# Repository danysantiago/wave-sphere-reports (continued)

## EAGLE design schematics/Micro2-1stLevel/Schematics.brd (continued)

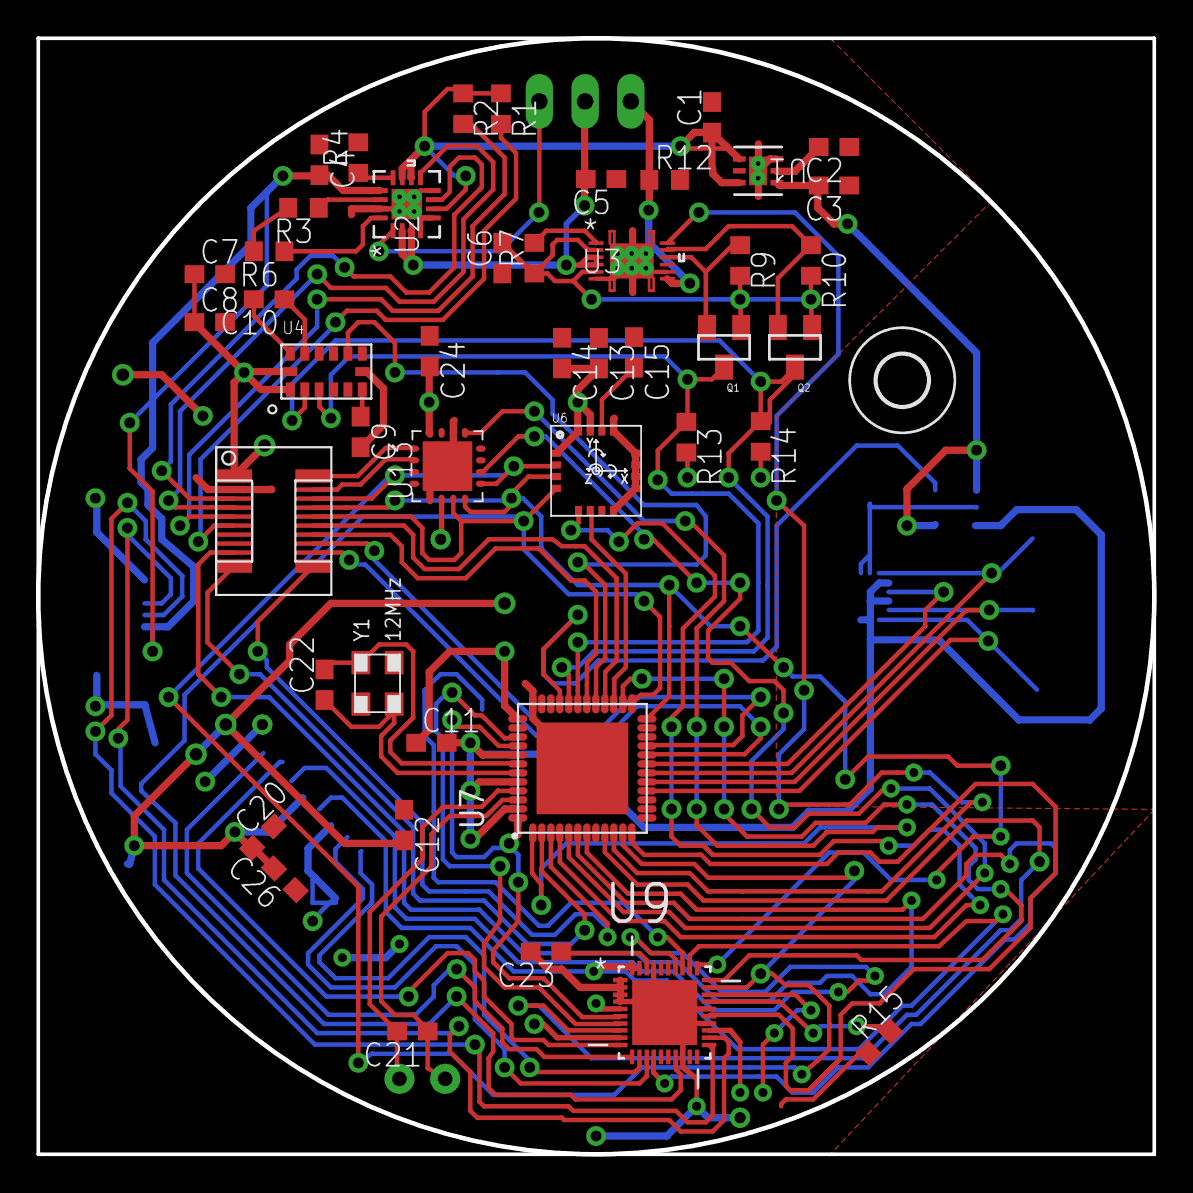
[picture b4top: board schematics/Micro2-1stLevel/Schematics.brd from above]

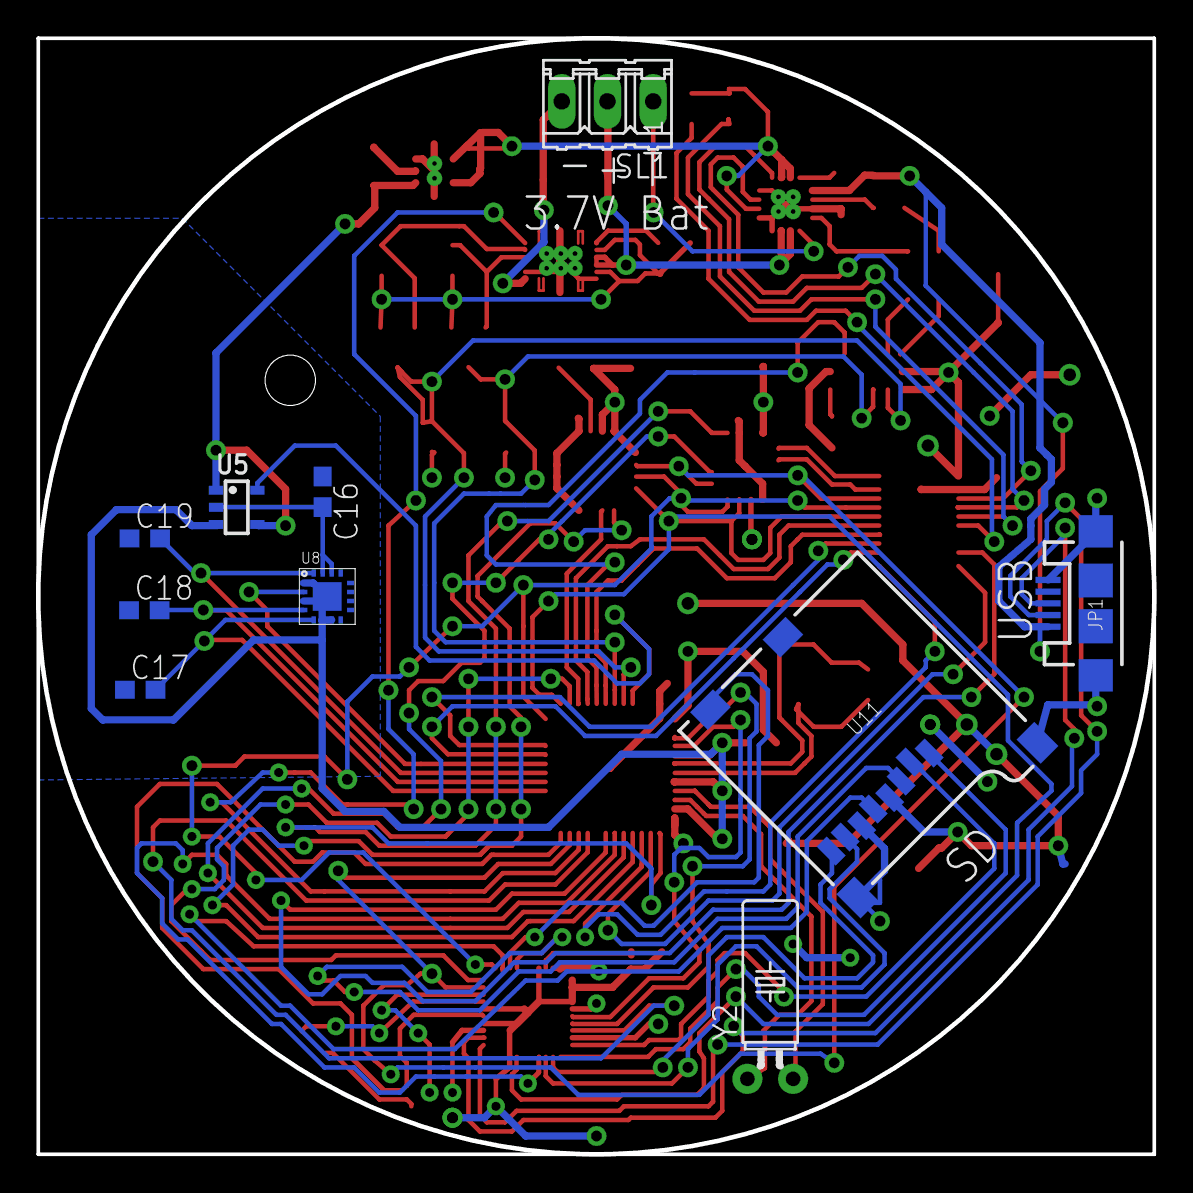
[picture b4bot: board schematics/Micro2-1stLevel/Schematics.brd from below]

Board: 4 copper layers, 62.0 x 62.0 mm, 56 parts (10 on the bottom side), 71 nets.

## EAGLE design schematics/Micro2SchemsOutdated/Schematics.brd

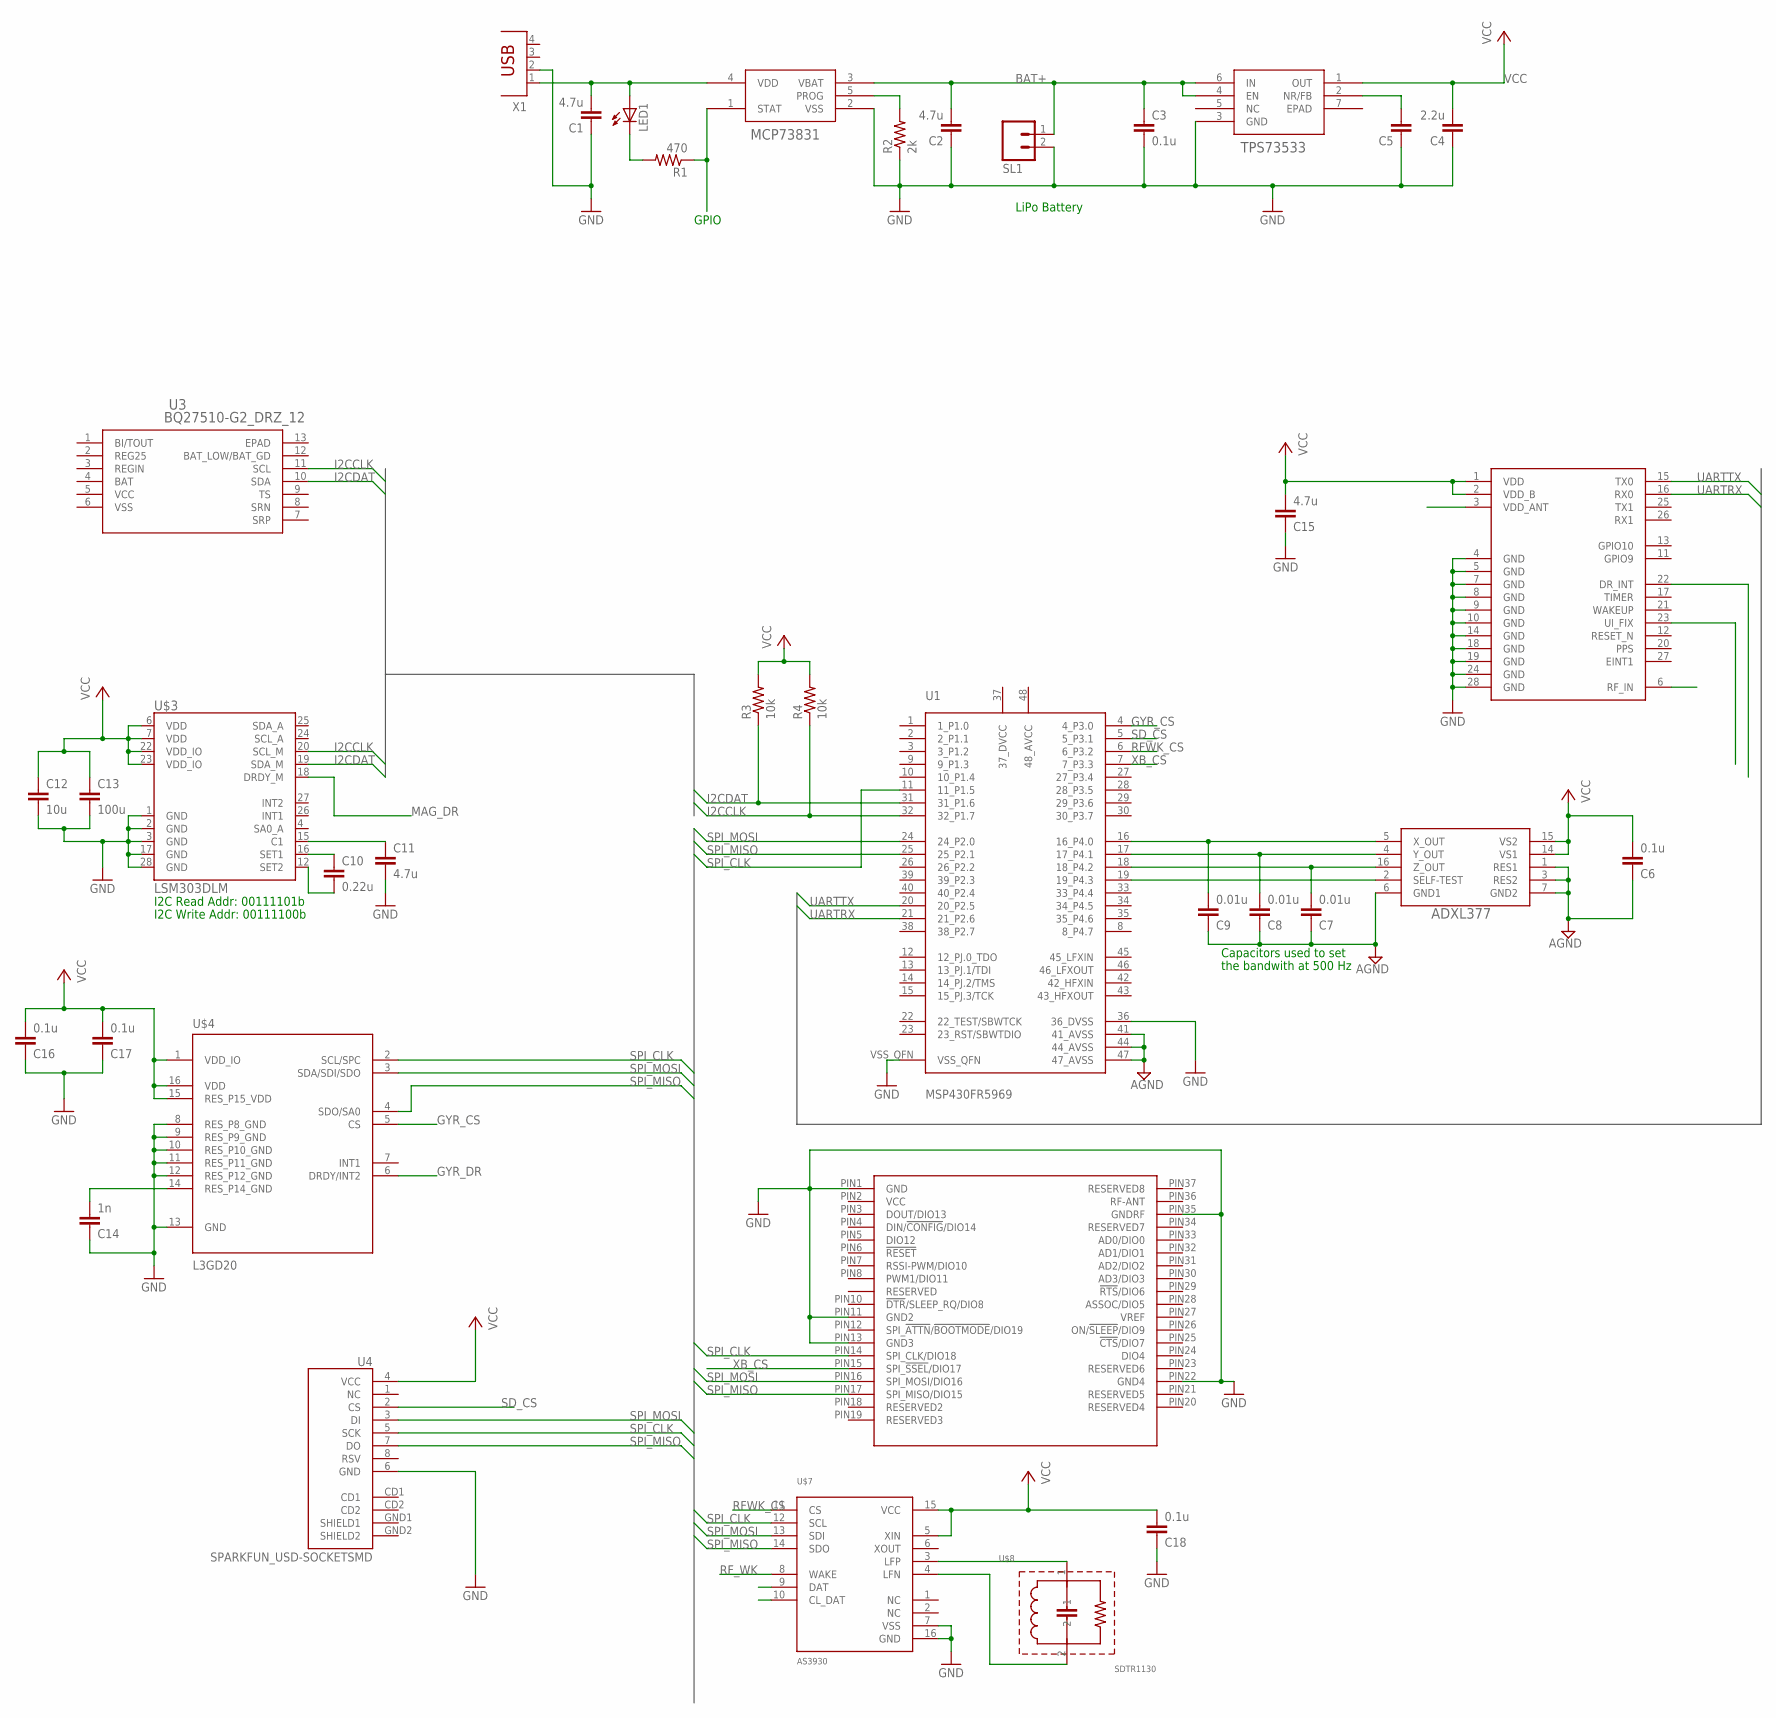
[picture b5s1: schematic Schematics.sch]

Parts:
C1, C2, C15: 4.7u; C025-025X050
C3: 0.1u; C025-024X044
C4: 2.2u; C025-025X050
C5: C-EU025-025X050; C025-025X050
C6, C16, C17, C18: 0.1u; C025-025X050
C7, C8, C9: 0.01u; C025-025X050
C10: 0.22u; C025-024X044
C11: 4.7u; C025-024X044
C12: 10u; C025-024X044
C13: 100u; C025-024X044
C14: 1n; C025-025X050
LED1: LED; SMARTLED-TTW
R1: 470; 0204V
R2: 2k; 0204V
R3, R4: 10k; 0204V
SL1: M02; 02P
U1: MSP430FR5969; RGZ(S-PQFP-N48)
U2: TPS73533_DRV_6; DRV6_1P6X1
U3: BQ27510-G2_DRZ_12; DRZ12_1P95X2P45
U4: SPARKFUN_USD-SOCKETSMD; SPARKFUN_MICRO-SD-SOCKET-PP
U$1: MCP73831-XXXX/OT; SOT-23-5_MC
U$2: ADXL377; LFCSP-16
U$3: LSM303DLM; LGA28-5X5
U$4: L3GD20
U$5: QUBIQ_XBEE-SMT; QUBIQ_FLAT-RF
U$6: IT530
U$7: AS3930
U$8: SDTR1130; SDTR1130-SMD
X1: PN61729

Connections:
AGND: C6.1, C7.1, C8.1, C9.1, U1.41 (41_AVSS), U1.44 (44_AVSS), U1.47 (47_AVSS), U$2.1 (RES1), U$2.3 (RES2), U$2.6 (GND1), U$2.7 (GND2)
BAT+: C2.2, C3.1, SL1.1, U2.4 (EN), U2.6 (IN), U$1.3 (VBAT)
EPAD: U3.13 (EPAD)
GND: C1.1, C2.1, C3.2, C4.1, C5.1, C11.2, C12.2, C13.2, C14.1, C15.1, C16.1, C17.1, C18.1, R2.1, SL1.2, U1.36 (36_DVSS), U1.VSS_QFN, U2.3 (GND), U4.6 (GND), U$1.2 (VSS), U$3.1 (GND), U$3.2 (GND), U$3.3 (GND), U$3.17 (GND), U$3.28 (GND), U$4.8 (RES_P8_GND), U$4.9 (RES_P9_GND), U$4.10 (RES_P10_GND), U$4.11 (RES_P11_GND), U$4.12 (RES_P12_GND), U$4.13 (GND), U$5.PIN1 (GND), U$5.PIN11 (GND2), U$5.PIN13 (GND3), U$5.PIN22 (GND4), U$5.PIN35 (GNDRF), U$6.4 (GND), U$6.5 (GND), U$6.7 (GND), U$6.8 (GND), U$6.9 (GND), U$6.10 (GND), U$6.14 (GND), U$6.18 (GND), U$6.19 (GND), U$6.24 (GND), U$6.28 (GND), U$7.7 (VSS), U$7.16 (GND), X1.2
GYR_CS: U1.4 (4_P3.0), U$4.5 (CS)
GYR_DR: U$4.6 (DRDY/INT2)
I2CCLK: R4.1, U1.32 (32_P1.7), U3.11 (SCL), U$3.20 (SCL_M)
I2CDAT: R3.1, U1.31 (31_P1.6), U3.10 (SDA), U$3.19 (SDA_M)
MAG_DR: U$3.18 (DRDY_M)
unnamed: C1.2, LED1.A@1 (A), U$1.4 (VDD), X1.1
unnamed: LED1.C@1 (C), R1.2
unnamed: R1.1, U$1.1 (STAT)
unnamed: R2.2, U$1.5 (PROG)
unnamed: U1.19 (19_P4.3), U$2.2 (SELF-TEST)
unnamed: C5.2, U2.2 (NR/FB)
unnamed: C14.2, U$4.14 (RES_P14_GND)
unnamed: C10.1, U$3.16 (SET1)
unnamed: C10.2, U$3.12 (SET2)
unnamed: C11.1, U$3.15 (C1)
unnamed: U$7.4 (LFN), U$8.2
unnamed: U$7.3 (LFP), U$8.1
unnamed: C9.2, U1.16 (16_P4.0), U$2.5 (X_OUT)
unnamed: C8.2, U1.17 (17_P4.1), U$2.4 (Y_OUT)
unnamed: C7.2, U1.18 (18_P4.2), U$2.16 (Z_OUT)
REG25: U3.2 (REG25)
REGIN: U3.3 (REGIN)
RFWK_CS: U1.6 (6_P3.2), U$7.11 (CS)
RF_WK: U$7.8 (WAKE)
SD_CS: U1.5 (5_P3.1), U4.2 (CS)
SPI_CLK: U1.11 (11_P1.5), U4.5 (SCK), U$4.2 (SCL/SPC), U$5.PIN14 (SPI_CLK/DIO18), U$7.12 (SCL)
SPI_MISO: U1.25 (25_P2.1), U4.7 (DO), U$4.4 (SDO/SA0), U$5.PIN17 (SPI_MISO/DIO15), U$7.14 (SDO)
SPI_MOSI: U1.24 (24_P2.0), U4.3 (DI), U$4.3 (SDA/SDI/SDO), U$5.PIN16 (SPI_MOSI/DIO16), U$7.13 (SDI)
UARTRX: U1.21 (21_P2.6), U$6.16 (RX0)
UARTTX: U1.20 (20_P2.5), U$6.15 (TX0)
VCC: C4.2, C6.2, C12.1, C13.1, C15.2, C16.2, C17.2, C18.2, R3.2, R4.2, U2.1 (OUT), U3.5 (VCC), U4.4 (VCC), U$2.14 (VS1), U$2.15 (VS2), U$3.6 (VDD), U$3.7 (VDD), U$3.22 (VDD_IO), U$3.23 (VDD_IO), U$4.1 (VDD_IO), U$4.15 (RES_P15_VDD), U$4.16 (VDD), U$6.1 (VDD), U$6.2 (VDD_B), U$7.5 (XIN), U$7.15 (VCC)
VSS: U3.6 (VSS)
XB_CS: U1.7 (7_P3.3), U$5.PIN15 (SPI_!SSEL!/DIO17)

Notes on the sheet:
LiPo Battery
GPIO
Capacitors used to set
I2C Read Addr: 00111101b
I2C Write Addr: 00111100b
the bandwith at 500 Hz

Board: 2 copper layers, 37 parts (0 on the bottom side), 30 nets, no tracks yet.

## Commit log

2013-02-04 Initial commit, uploading proposal
2013-02-06 Creating document for Progress Report #2
2013-02-06 Fixed Work Distribution Table and added it to report
2013-02-06 Fixed error in Work Distribution Table
2013-02-08 Fixed Work Distribution
2013-02-10 Added flowchart section
2013-02-10 Modified README
2013-02-10 Added Pin count table
2013-02-10 Ignoring report.pdf
2013-02-10 Commiting pdf...
2013-02-10 Added specific ignore for report.pdf
2013-02-10 Fixed ignore
2013-02-10 Removed report.pdf from tracked files
2013-02-10 Added Flowcharts
2013-02-10 Added specifications table
2013-02-10 Added Global System View
2013-02-10 Finished rough draft of Pin Count section and added References
2013-02-10 Adding References
2013-02-10 Changed global system view
2013-02-10 Explained each flowchart and updated flowchart images
2013-02-10 Fixed block diagram and wrote description
2013-02-10 Fixed presentation page
2013-02-10 added mcu comparation table (mcu selection)
2013-02-10 partially fixed table formatting
2013-02-11 added mcu to table mcu selection table
2013-02-11 eliminated 2 mcus in mcu selection
2013-02-11 Modified flowcharts and proof read the operating modes paragraphs
2013-02-11 Added MCU selection paragraph
2013-02-11 Updated standby flowchart, added SD information is how much free space it has
2013-02-11 Changed MCU selection table
2013-02-11 Re-Fixed MCU selection table
2013-02-11 added preliminar poster
2013-02-11 changed GSV1 image
2013-02-11 Fixed some typos on mcuSelection.tex
2013-02-11 Fixed typos and grammatical errors in flowchart.tex.
2013-02-11 added additional GSV pictures and did a rough explanation
2013-02-11 changed GSV pictures
2013-02-11 Added Battery Charge Methods
2013-02-12 Wrote Wireless Charging paragraph
2013-02-12 Added USB Charging subsubsection. Writing about charge management controllers and whatnot.
2013-02-12 Divided paragraphs of USB Charging subsubsection
2013-02-12 Added space between paragraphs on charging methods
2013-02-12 Fixed typos
2013-02-12 Updated pin count
2013-02-12 fixed components and mcu tables
2013-02-12 Modified mcu selection, explained better why the CC420 was not choosen
2013-02-12 added poster and new block diagram
2013-02-12 fixed some errors in mcu selection
2013-02-12 fixed some things that did not make sense
2013-02-12 Removed Power Management Components
2013-02-12 Added Qi Standard reference
2013-02-12 changed xbee
2013-02-12 Explained RF Wake-Up Receiver
2013-02-12 fixed components specifications, again..
2013-02-12 Fixed typos and grammatical errors throughout the document.
2013-02-12 Proofread Sections 1 and 2, still working on the other ones
2013-02-12 Added LED Power On into the Locate Mode flowchart. Revisited the RF Wake-Up Receiver paragraph.
2013-02-12 Finished reading and making corrections
2013-02-12 Fixed some typos, revisited flowcharts
2013-02-12 fixed locate mode flow chart size
2013-02-12 fixed some typos
2013-02-12 Citing USB references
2013-02-12 Specified that the power dissipation from linear topology in USB charging is as heat in the USB cable.
2013-02-12 Resized system flowchart
2013-02-27 Initial commit for Report 3
2013-02-27 added super pretty Software Plan
2013-02-28 Added Flow Charts, created flow chart sections (needs fix), fixed algorithm in software plan and added a tentative description for software plan
2013-02-28 Adding eagle schematics and library
2013-02-28 forgot gitignore
2013-03-03 changed sampling event service flow chart and pseudocode
2013-03-03 changed location flow chart
2013-03-03 Fixed the flowchart description paragraphs.
2013-03-03 changed location flowchart and pseudocode, began timing analysis
2013-03-03 Added report.pdf to gitignore
2013-03-04 Worked on timing analysis.
2013-03-04 little changes to timing analysis
2013-03-04 Working on time analysis. Changed crystal to 38.4kHz.
2013-03-04 changed component frequencies table in timing analysis and added partial part list
2013-03-04 Added a line, deleted a couple others.
2013-03-04 added point2point timing table to timing analysis
2013-03-04 added some files for missing sections and wrote some simple stuff for each
2013-03-04 Fixed typo in input file.
2013-03-05 added logic compatibility table to power analysis
2013-03-05 changed timing tables (added/removed signals
2013-03-05 Added First part of power analysis
2013-03-05 Added explanation for use of 12MHz crystal
2013-03-05 Finsihed power analysis
2013-03-05 Added Components List
2013-03-05 Added schematics.
2013-03-05 added block diagram
2013-03-05 Changed schematic
2013-03-05 Did stuff.
2013-03-05 Updated block diagram. Changed title of Power block.
2013-03-05 Proofread flowchart section.
2013-03-05 Fixed all tables
2013-03-05 Proofread timing analysis section.
2013-03-05 Proofreading Power Analysis.
2013-03-05 changed flow charts
2013-03-05 Did stuff
2013-03-05 Proofread power analysis.
2013-03-05 Modified Git Ignore
2013-03-05 Proofread block diagram
2013-03-05 Fixed algorithm positioning
2013-03-05 Added battery to part list
2013-03-05 Added References
2013-03-05 final report stuff
2013-03-12 Added Thermal Analysis
2013-03-13 Finished Thermal Analysis
2013-03-28 Added Progress Report 4 File
2013-03-29 added sec - hw components
2013-03-29 added new system flow chart
2013-03-29 Added thermal analysis file
2013-03-29 changed sd thingy to sd card
2013-03-29 Finsihed revised thermal Analysis
2013-03-31 changed system flow chart
2013-04-07 Added Schematics to keep them safe
2013-04-07 Adding 2 level schematic
2013-04-07 Added pdf of schematics and board
2013-04-07 Added full schematics pdf
2013-04-07 added schematics section
2013-04-07 changen aesthetics in hardware components
2013-04-07 did some changes in flow chart section
2013-04-08 changed block diagram
    added a rough explanation of the changes in battery meter, battery
    charger, xbee and gps
2013-04-08 added timing analysis
2013-04-08 added comp freqs to timing analysis
2013-04-09 Fixed Complete Schematics and removed two layer schematics because they are not clear
2013-04-09 Fixed typos.
2013-04-09 changed hw comp table..
2013-04-09 more changes to hw comp table
2013-04-09 Fixed some typos, changed some sentences. No big deal.
2013-04-09 added GUI stuff
2013-04-09 Added timing analysis timebases and stuff.
2013-04-09 Proofread document
2013-04-09 Elaborated into some details of the PCB design
2013-04-09 proofread document, added flow chart changes
2013-04-09 changed i2c to i^2c
2013-04-21 Minor unsaved changes
2013-04-24 Added Report #5 and deliverables table with space for professor annotations
2013-04-27 Finished Progress Report 5
2013-04-27 Added Final report structure document along with several sections copied from previous reports
2013-04-29 Added PCB files, GDrive and Dropbox weren't playing nicely
2013-04-29 Added GPS_FIX Led to 2nd lvl
2013-04-29 Updated schematic values
2013-04-29 Commited gerber files
2013-05-01 Finished Power and worked on Block Diagram sections
2013-05-01 Finished Block Diagram
2013-05-01 Added missing files that might make previous verions of the document not work properly
2013-05-01 Added System overview paragraph and image
2013-05-01 updated component frequencies' table
2013-05-01 fixed typo
2013-05-01 stuff
2013-05-02 Some progress
2013-05-02 added full schematic
2013-05-03 changed block diagram
2013-05-03 user guide doc
2013-05-03 Finished some sections
2013-05-03 work distribution updated
2013-05-03 Modified 1st lvl schematic, changed gyro to i2c, board still needs update
2013-05-03 Added Memory Map and Schematics
2013-05-03 Timing analysis
2013-05-03 Added more sections, only theoretical background remains. Almost there...
2013-05-03 Erorr in work distribution
2013-05-03 some typos and fixed error in user guide
2013-05-03 changed user guide page numbers
2013-05-03 added remaining flow charts in appendix
2013-05-03 Finished theoretical background
2013-05-03 Compiled and Done
2013-05-03 changed status event flow chart
    the other one was ugly
2013-05-11 Added report for ADC - TI
